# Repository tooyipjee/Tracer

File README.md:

# Tracer: A Wearable for Things 🚀

## High-Level Summary

Introducing "Tracer" - a dynamic, open-source project built on the ESP-32 platform. Tailored for enthusiasts and innovators, Tracer taps into the vast array of software libraries available for the ESP-32. It offers a unique window into the intricate processes and algorithms behind creating a personalized fitness tracker.

Available on 

---

## Detailed Description

### What is it?

Tracer is a versatile wearable designed for a myriad of applications. Whether you're a sports enthusiast wanting to analyze your tennis serve or a cyclist keen on understanding lean angles, Tracer provides invaluable insights. Key features include:

- **Real-time Object Tracking:** Utilize the LSM6DSL for precise motion capture.
- **Versatile Mounting:** High-quality velcro straps ensure adaptability, from monitoring lean angles on bicycles to analyzing tennis racquet poses.
- **Battery Management:** Efficient on-board Li-ion battery charging via the TP4065.
- **Extended Battery Life:** Up to 2.5 hours of continuous BLE streaming at 10Hz.
- **Proven Connectivity:** Boasts a 15m BLE range in open spaces, as tested on a tennis court.

---

## Use Cases

Tracer's design closely integrates with the Madgwick Filter, facilitating sensor fusion to estimate heading, roll, and pitch. This data can be transmitted to devices like smartphones or PCs for further analysis. Here are some applications:

## Use Cases

Tracer's design closely integrates with the Madgwick Filter, facilitating sensor fusion to estimate heading, roll, and pitch. This data can be transmitted to devices like smartphones or PCs for further analysis. Here are some applications:

- **Real-time 3D Visualization:** Stream data via UART to a script on [Processing](https://github.com/processing) for a 3D visual experience. Watch the demonstration [here](https://www.youtube.com/watch?v=f6d10yX7fZ4).

- **Stream to Phyphox:** Directly stream IMU plots over BLE to your phone. Export data as CSV for in-depth analysis, showcasing Tracer's capability to track accelerometer data and tennis ball strikes. Check out the live demo [here](https://www.youtube.com/watch?v=bZTHZ-QFxR4).

- **Gesture Recognition with Edge Impulse:** Highlighting Tracer's adaptability, the Edge Impulse platform can be employed to train a neural network. This network operates natively on the ESP32, tracking specific gestures or activities. See it in action [here](https://www.youtube.com/watch?v=aU7HlFeuip4).

---

## How to Run the Demo Script

1. **Setup:** Ensure you have the Arduino IDE installed on your computer.
2. **Connect:** Plug in your ESP32-C3 device to your computer via USB.
3. **Integrated JTAG:** Ensure the JTAG is setup. In Tools, "USB CDC On Boot" is Enabled and JTAG Adapter is USB JTAG Adapter.
5. **Load Script:** Open one of the demo script provided in the Arduino IDE.
6. **Select Board:** From the 'Tools' menu, select 'Board' and choose 'ESP32-C3'.
7. **Select Port:** Select the port for the Tracer device, if nothing pops up, unplug the device, hold the settings button and plug it back into the computer while still holding the button. It should appear now.
8. **Upload:** Click on the 'Upload' button to program the ESP32-C3.
9. **Monitor:** Open the Serial Monitor to view outputs and ensure the script runs successfully.

For any issues or further instructions, please refer to the documentation or raise an issue in the repo.

**Acknowledgments:** A special thank you to JLCPCB for their invaluable support in sponsoring this project. Their expertise has been instrumental, allowing for rapid prototyping without sacrificing quality.

---

## License

MIT License

Copyright (c) 2023 elektroThing

Permission is hereby granted, free of charge, to any person obtaining a copy
of this software and associated documentation files (the "Software"), to deal
in the Software without restriction, including without limitation the rights
to use, copy, modify, merge, publish, distribute, sublicense, and/or sell
copies of the Software, and to permit persons to whom the Software is
furnished to do so, subject to the following conditions:

The above copyright notice and this permission notice shall be included in all
copies or substantial portions of the Software.

THE SOFTWARE IS PROVIDED "AS IS", WITHOUT WARRANTY OF ANY KIND, EXPRESS OR
IMPLIED, INCLUDING BUT NOT LIMITED TO THE WARRANTIES OF MERCHANTABILITY,
FITNESS FOR A PARTICULAR PURPOSE AND NONINFRINGEMENT. IN NO EVENT SHALL THE
AUTHORS OR COPYRIGHT HOLDERS BE LIABLE FOR ANY CLAIM, DAMAGES OR OTHER
LIABILITY, WHETHER IN AN ACTION OF CONTRACT, TORT OR OTHERWISE, ARISING FROM,
OUT OF OR IN CONNECTION WITH THE SOFTWARE OR THE USE OR OTHER DEALINGS IN THE
SOFTWARE.

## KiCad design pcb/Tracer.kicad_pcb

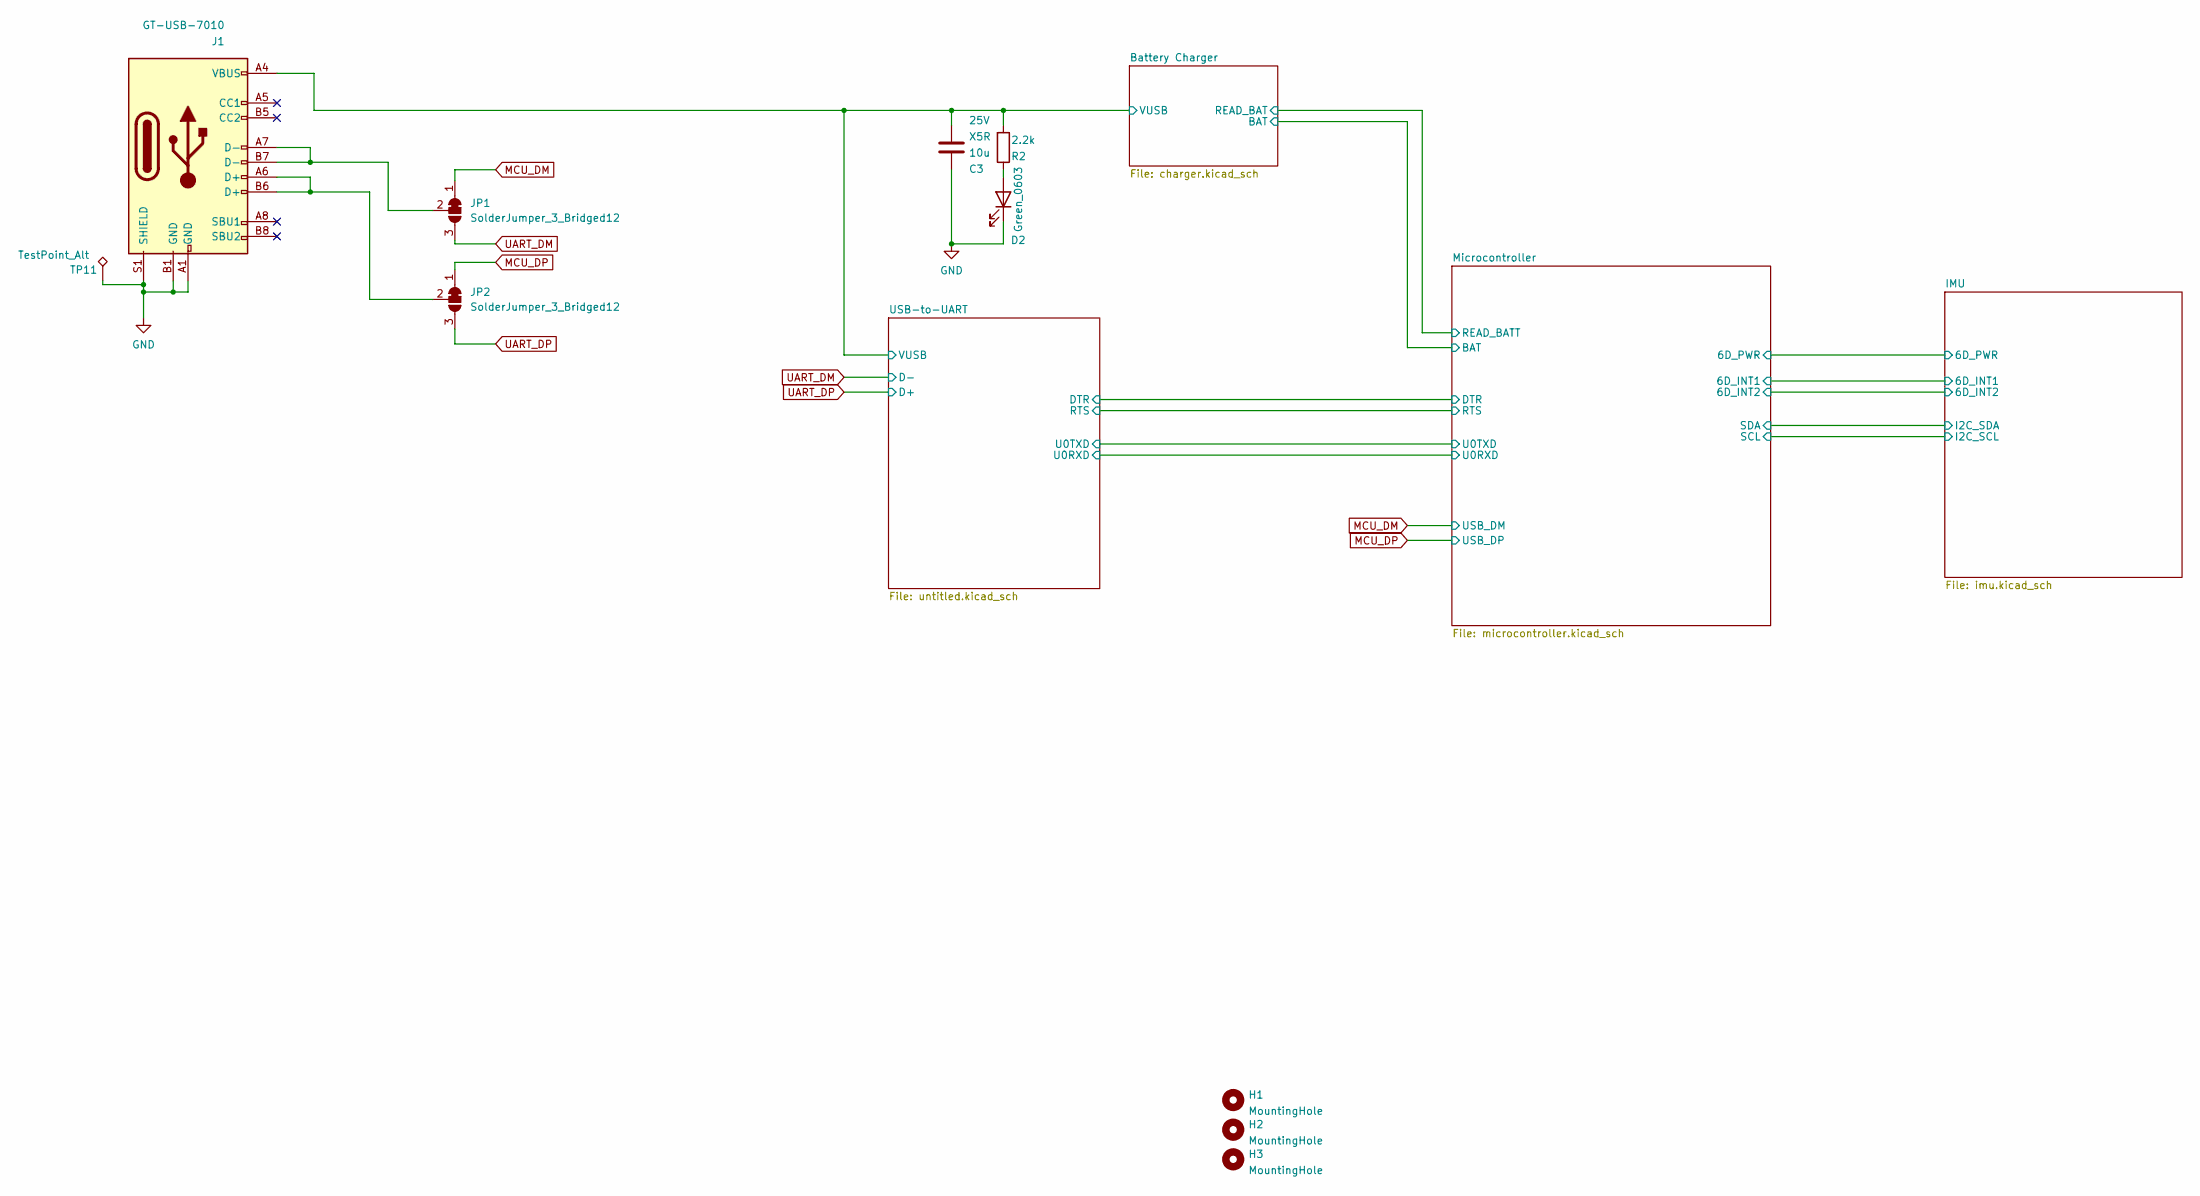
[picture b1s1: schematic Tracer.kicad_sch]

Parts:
C3: 10u; C_0805_2012Metric; Voltage 25V; LCSC C15850
D2: Green_0603; LED_0603_1608Metric; LCSC C72043
H1, H2, H3: MountingHole; MountingHole_2.2mm_M2_Small
J1: GT-USB-7010; GT-USB-7010A; LCSC C963370
JP1, JP2: SolderJumper_3_Bridged12; SolderJumper-3_P1.3mm_Bridged12_Pad1.0x1.5mm_NumberLabels
R2: 2.2k; R_0402_1005Metric; LCSC C25879
TP11: TestPoint_Alt; TestPoint_Pad_1.0x1.0mm

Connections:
/Battery Charger/VUSB: C3.2, J1.A4 (VBUS), J1.A9 (VBUS), J1.B4 (VBUS), J1.B9 (VBUS), R2.2; also elsewhere on the board
GND: C3.1, D2.1 (K), J1.A1 (GND), J1.B1 (GND), J1.S1 (SHIELD), TP11.1; also elsewhere on the board
MCU_DM: JP1.1 (A); also elsewhere on the board
MCU_DP: JP2.1 (A); also elsewhere on the board
unnamed: D2.2 (A), R2.1
unnamed: J1.A7 (D-), J1.B7 (D-), JP1.2 (C)
unnamed: J1.A6 (D+), J1.B6 (D+), JP2.2 (C)
UART_DM: JP1.3 (B); also elsewhere on the board
UART_DP: JP2.3 (B); also elsewhere on the board

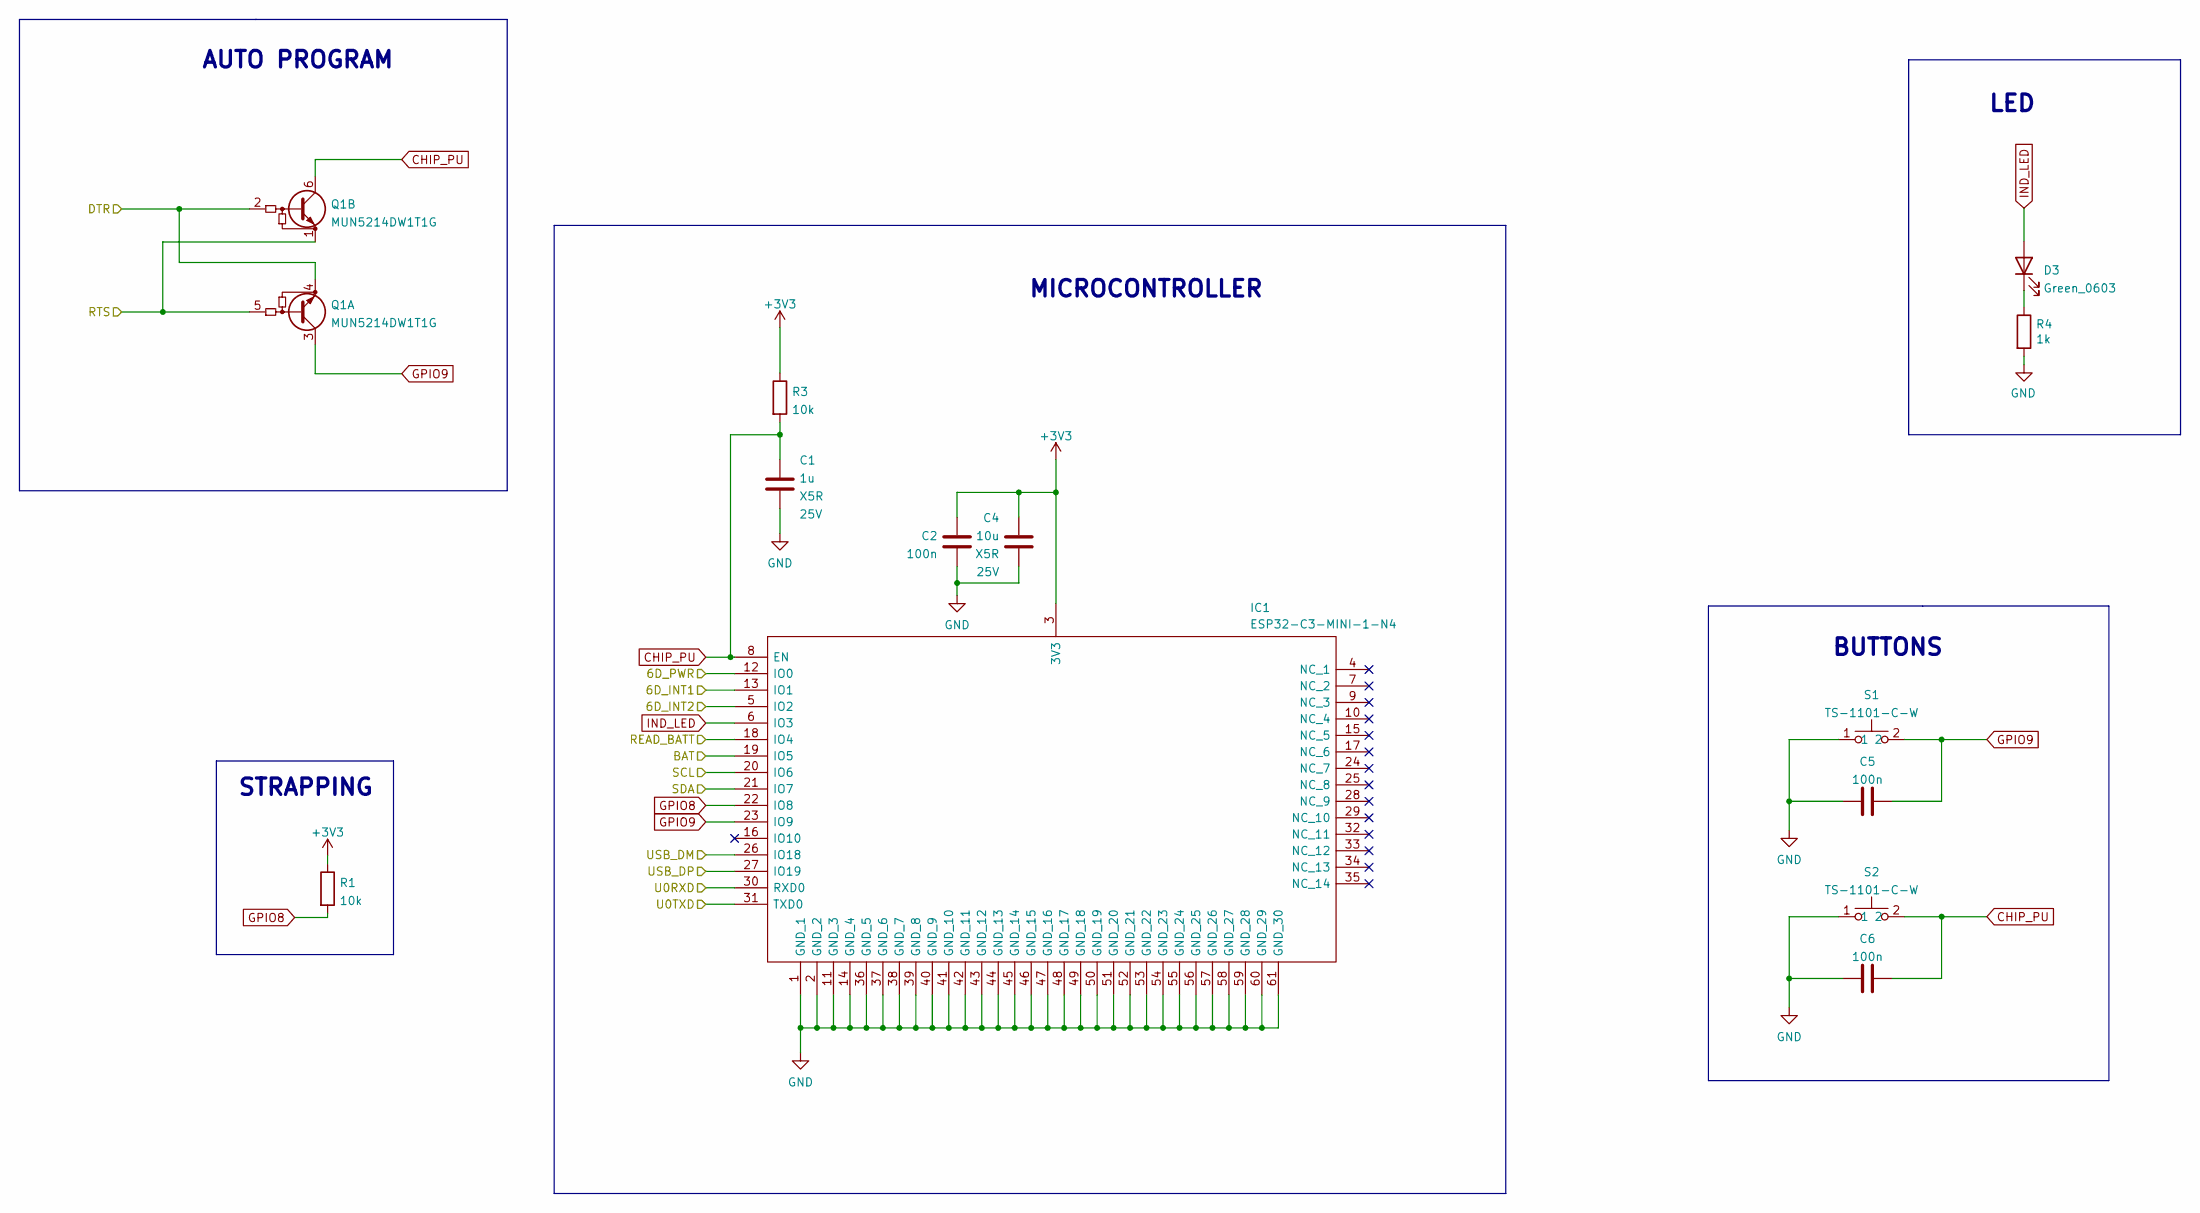
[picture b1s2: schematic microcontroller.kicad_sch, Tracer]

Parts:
C1: 1u; C_0402_1005Metric; Voltage 25V; LCSC C52923
C2, C5, C6: 100n; C_0402_1005Metric; LCSC C307331
C4: 10u; C_0805_2012Metric; Voltage 25V; LCSC C15850
D3: Green_0603; LED_0603_1608Metric; LCSC C72043
IC1: ESP32-C3-MINI-1-N4; ESP32C3MINI1N4; Manufacturer_Part_Number ESP32-C3-MINI-1-N4; Mouser Part Number 356-ESP32-C3-MINI1N4
Q1: MUN5214DW1T1G; SOT-363_SC-70-6; LCSC C94403
R1, R3: 10k; R_0402_1005Metric; LCSC C25744
R4: 1k; R_0402_1005Metric; LCSC C11702
S1, S2: TS-1101-C-W; TS1101CW; Manufacturer_Part_Number TS-1101-C-W; LCSC C318938

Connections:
+3V3: C2.1, C4.1, IC1.3 (3V3), R1.1, R3.1; also elsewhere on the board
/Battery Charger/BAT: IC1.19 (IO5); also elsewhere on the board
/Battery Charger/READ_BAT: IC1.18 (IO4); also elsewhere on the board
/IMU/6D_INT1: IC1.13 (IO1); also elsewhere on the board
/IMU/6D_INT2: IC1.5 (IO2); also elsewhere on the board
/IMU/6D_PWR: IC1.12 (IO0); also elsewhere on the board
/IMU/I2C_SCL: IC1.20 (IO6); also elsewhere on the board
/IMU/I2C_SDA: IC1.21 (IO7); also elsewhere on the board
/Microcontroller/DTR: Q1.2 (B2), Q1.4 (E1); also elsewhere on the board
/Microcontroller/RTS: Q1.1 (E2), Q1.5 (B1); also elsewhere on the board
/Microcontroller/U0RXD: IC1.30 (RXD0); also elsewhere on the board
/Microcontroller/U0TXD: IC1.31 (TXD0); also elsewhere on the board
CHIP_PU: C1.1, C6.2, IC1.8 (EN), Q1.6 (C2), R3.2, S2.2
GND: C1.2, C2.2, C4.2, C5.1, C6.1, IC1.1 (GND_1), IC1.2 (GND_2), IC1.11 (GND_3), IC1.14 (GND_4), IC1.36 (GND_5), IC1.37 (GND_6), IC1.38 (GND_7), IC1.39 (GND_8), IC1.40 (GND_9), IC1.41 (GND_10), IC1.42 (GND_11), IC1.43 (GND_12), IC1.44 (GND_13), IC1.45 (GND_14), IC1.46 (GND_15), IC1.47 (GND_16), IC1.48 (GND_17), IC1.49 (GND_18), IC1.50 (GND_19), IC1.51 (GND_20), IC1.52 (GND_21), IC1.53 (GND_22), IC1.54 (GND_23), IC1.55 (GND_24), IC1.56 (GND_25), IC1.57 (GND_26), IC1.58 (GND_27), IC1.59 (GND_28), IC1.60 (GND_29), IC1.61 (GND_30), R4.2, S1.1, S2.1; also elsewhere on the board
GPIO8: IC1.22 (IO8), R1.2
GPIO9: C5.2, IC1.23 (IO9), Q1.3 (C1), S1.2
IND_LED: D3.2 (A), IC1.6 (IO3)
MCU_DM: IC1.26 (IO18); also elsewhere on the board
MCU_DP: IC1.27 (IO19); also elsewhere on the board
unnamed: D3.1 (K), R4.1

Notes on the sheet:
MICROCONTROLLER
LED
AUTO PROGRAM
BUTTONS
STRAPPING

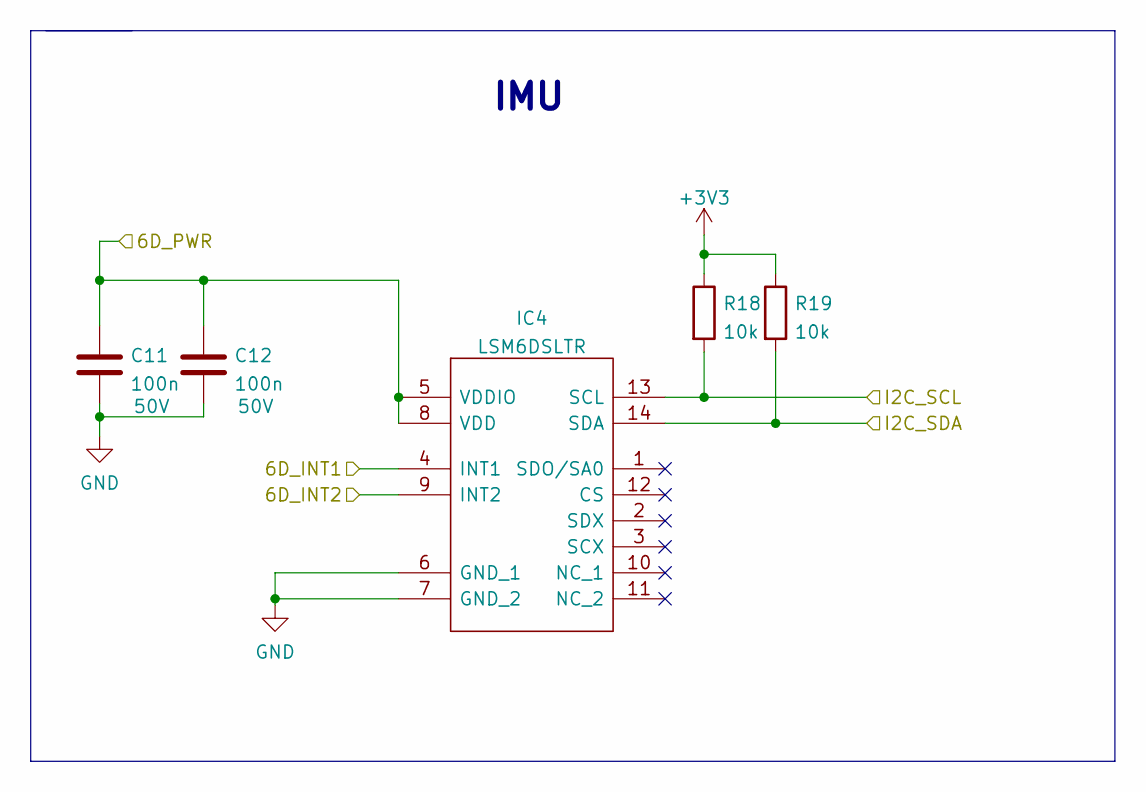
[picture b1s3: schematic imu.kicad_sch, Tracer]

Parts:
C11, C12: 100n; C_0402_1005Metric; Voltage 50V; LCSC C307331
IC4: LSM6DSLTR; Manufacturer_Part_Number LSM6DSLTR; Mouser Part Number 511-LSM6DSLTR
R18, R19: 10k; R_0402_1005Metric; LCSC C25744

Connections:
+3V3: R18.1, R19.1; also elsewhere on the board
/IMU/6D_INT1: IC4.4 (INT1); also elsewhere on the board
/IMU/6D_INT2: IC4.9 (INT2); also elsewhere on the board
/IMU/6D_PWR: C11.1, C12.1, IC4.5 (VDDIO), IC4.8 (VDD); also elsewhere on the board
/IMU/I2C_SCL: IC4.13 (SCL), R18.2; also elsewhere on the board
/IMU/I2C_SDA: IC4.14 (SDA), R19.2; also elsewhere on the board
GND: C11.2, C12.2, IC4.6 (GND_1), IC4.7 (GND_2); also elsewhere on the board

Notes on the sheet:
IMU

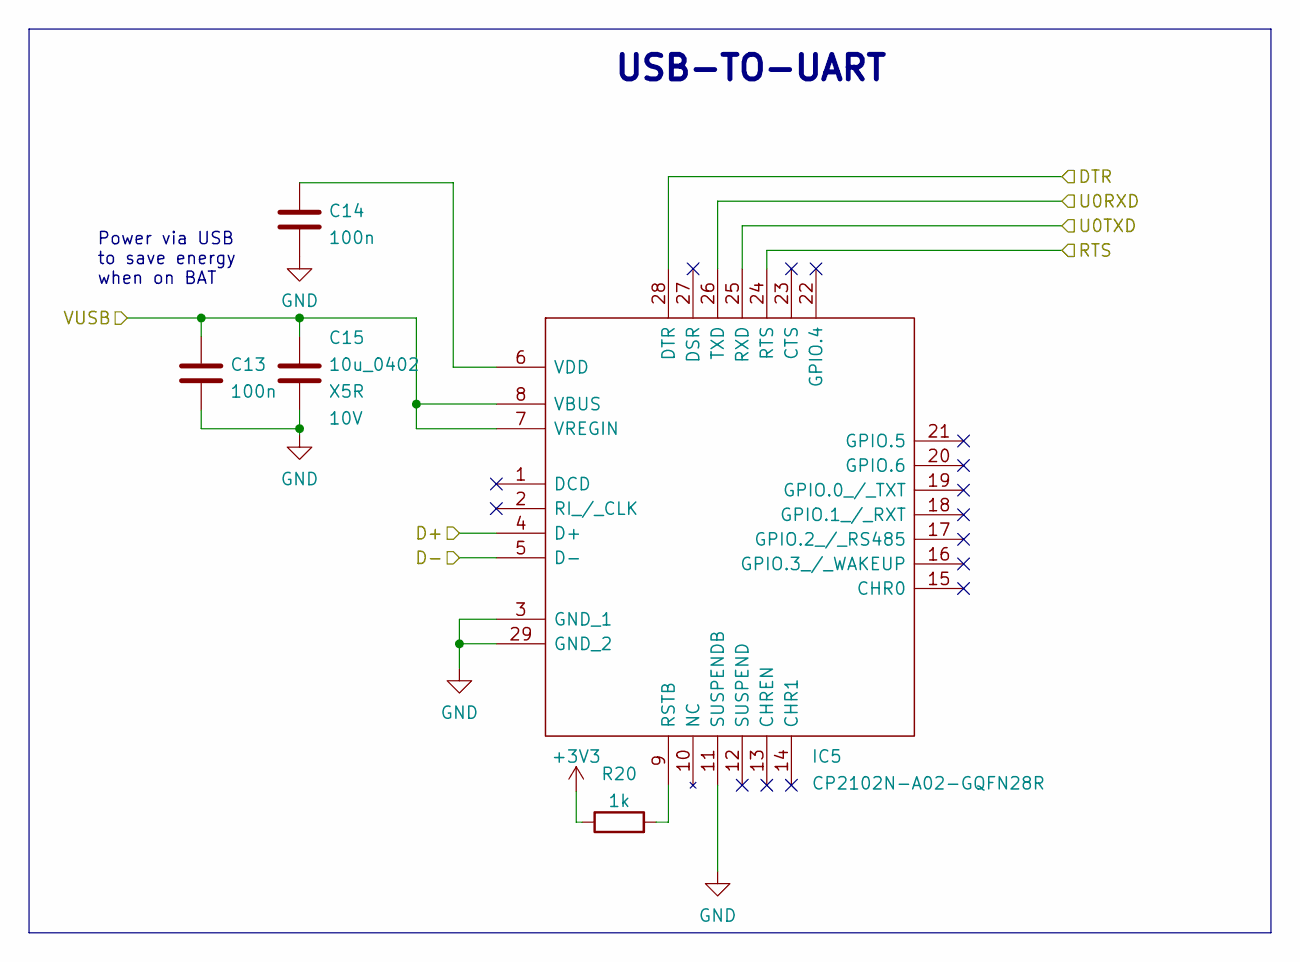
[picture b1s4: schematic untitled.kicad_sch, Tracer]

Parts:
C13, C14: 100n; C_0402_1005Metric; LCSC C307331
C15: 10u_0402; C_0402_1005Metric; Voltage 10V; LCSC C315248
IC5: CP2102N-A02-GQFN28R; QFN50P500X500X80-29N-D; Manufacturer_Part_Number CP2102N-A02-GQFN28R; Mouser Part Number 634-CP2102NA02QFN28R
R20: 1k; R_0402_1005Metric; LCSC C11702

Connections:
+3V3: R20.1; also elsewhere on the board
/Battery Charger/VUSB: C13.1, C15.1, IC5.7 (VREGIN), IC5.8 (VBUS); also elsewhere on the board
/Microcontroller/DTR: IC5.28 (DTR); also elsewhere on the board
/Microcontroller/RTS: IC5.24 (RTS); also elsewhere on the board
/Microcontroller/U0RXD: IC5.26 (TXD); also elsewhere on the board
/Microcontroller/U0TXD: IC5.25 (RXD); also elsewhere on the board
GND: C13.2, C14.2, C15.2, IC5.3 (GND_1), IC5.11 (SUSPENDB), IC5.29 (GND_2); also elsewhere on the board
unnamed: IC5.9 (RSTB), R20.2
unnamed: C14.1, IC5.6 (VDD)
UART_DM: IC5.5 (D-); also elsewhere on the board
UART_DP: IC5.4 (D+); also elsewhere on the board

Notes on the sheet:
USB-TO-UART
Power via USB to save energy when on BAT

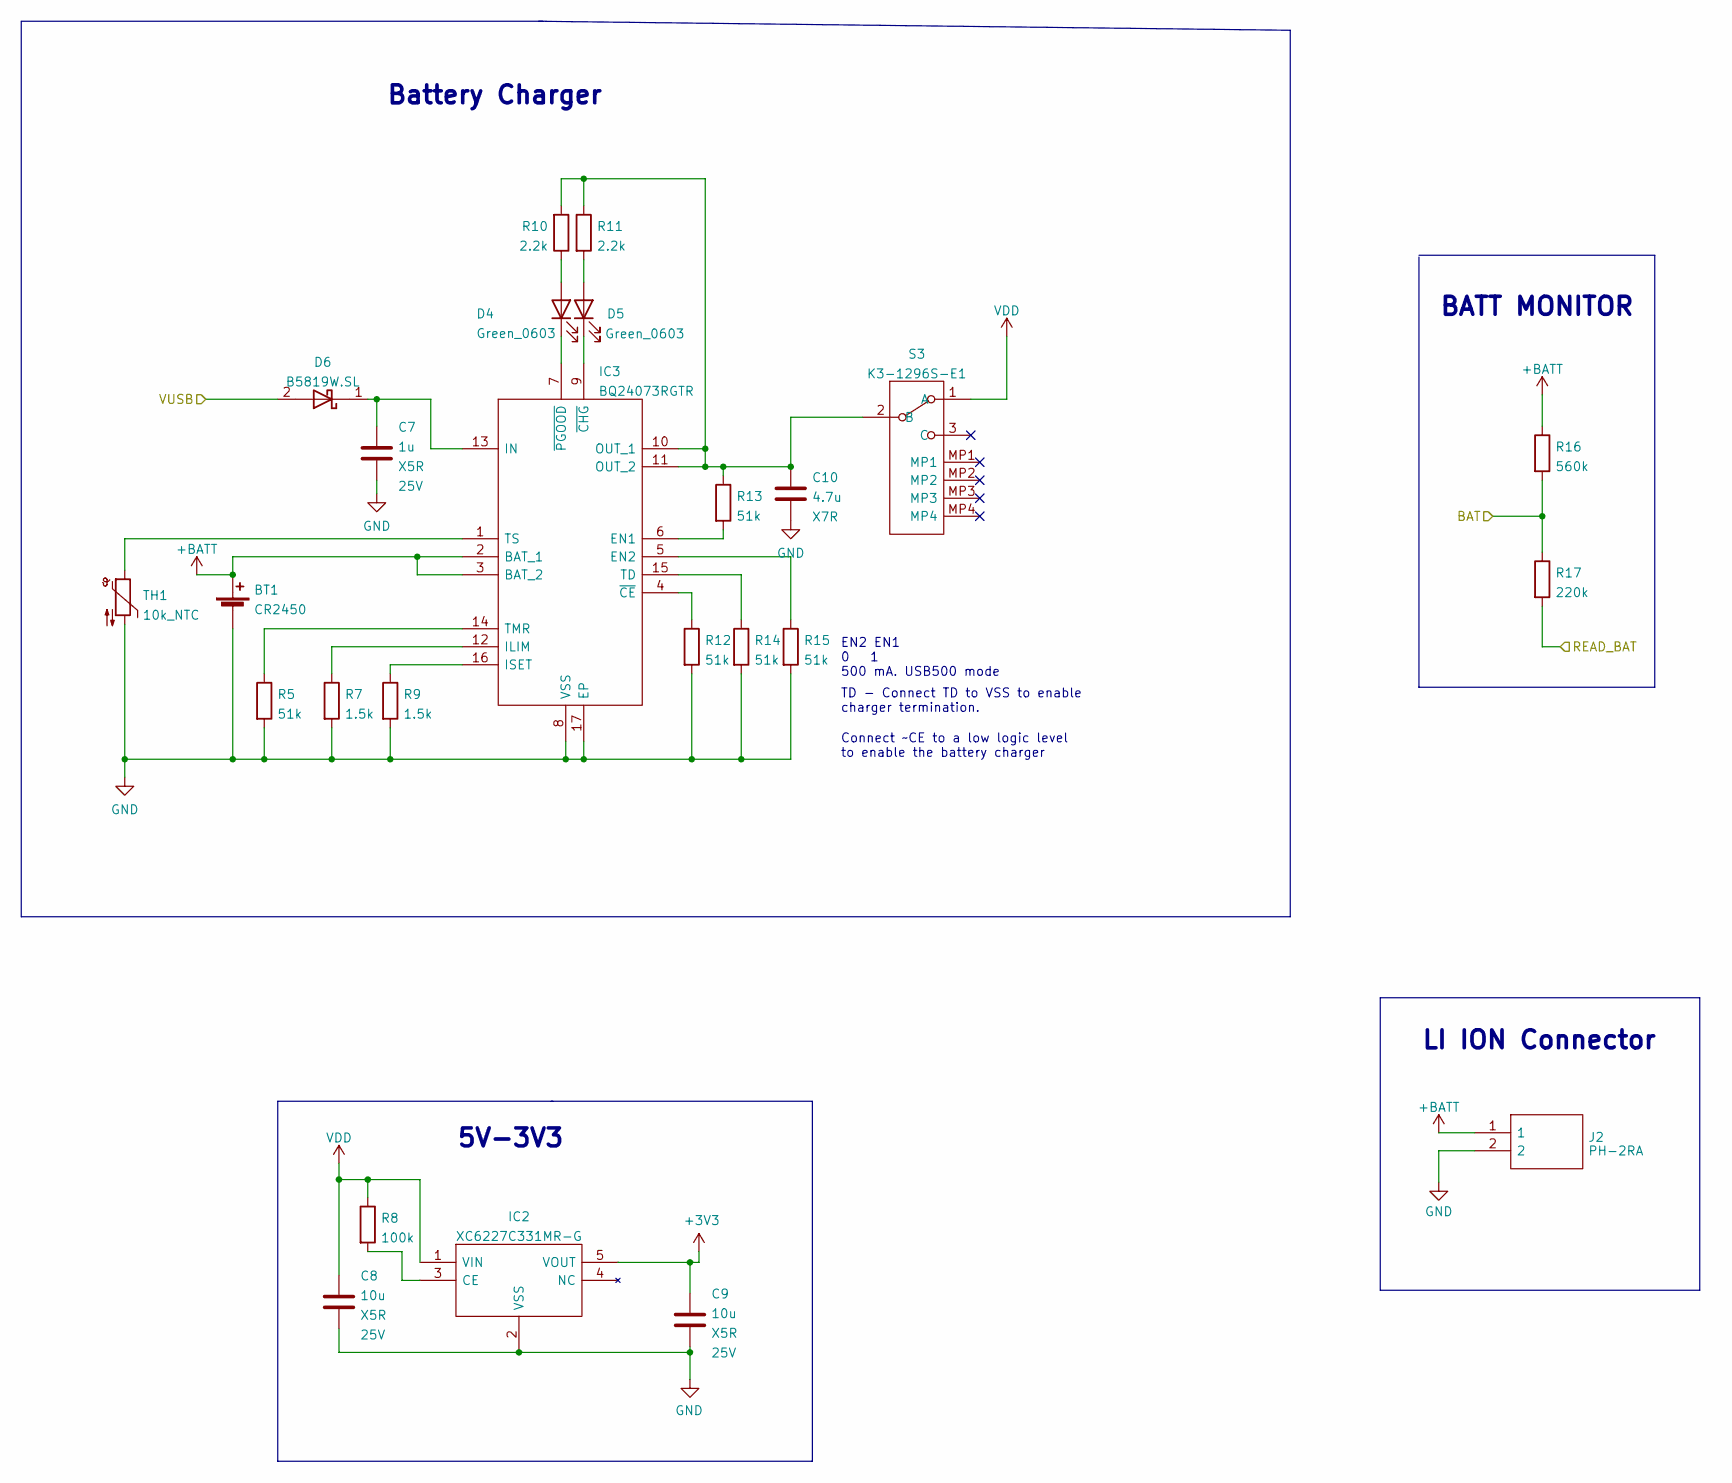
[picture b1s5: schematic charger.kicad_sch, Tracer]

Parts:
BT1: CR2450; BS-24-B4AK014; LCSC C964813
C7: 1u; C_0402_1005Metric; Voltage 25V; LCSC C52923
C8, C9: 10u; C_0805_2012Metric; Voltage 25V; LCSC C15850
C10: 4.7u; C_1206_3216Metric; Rating 50V; LCSC C29823
D4, D5: Green_0603; LED_0603_1608Metric; LCSC C72043
D6: B5819W.SL; B5819WSL; Manufacturer_Part_Number B5819W.SL; LCSC C8598
IC2: XC6227C331MR-G; SOT95P280X130-5N; Manufacturer_Part_Number XC6227C331MR-G; Mouser Part Number 865-XC6227C331MR-G
IC3: BQ24073RGTR; QFN50P300X300X100-17N-D; Manufacturer_Part_Number BQ24073RGTR; Mouser Part Number 595-BQ24073RGTR
J2: PH-2RA; SHDRRA2W50P0X200_1X2_600X760X510P; Manufacturer_Part_Number A2001WR-2P Thru-hole; Mouser Part Number 763-A2001WR2P
R5, R12, R13, R14, R15: 51k; R_0402_1005Metric; LCSC C25794
R7, R9: 1.5k; R_0402_1005Metric; LCSC C25867
R8: 100k; R_0402_1005Metric; LCSC C25741
R10, R11: 2.2k; R_0402_1005Metric; LCSC C25879
R16: 560k; R_0603_1608Metric; LCSC C23203
R17: 220k; R_0402_1005Metric; LCSC C25767
S3: K3-1296S-E1; K31296SE1; Manufacturer_Part_Number K3-1296S-E1; LCSC C128955
TH1: 10k_NTC; R_0402_1005Metric; MPN NCU15XH103F6SRC; LCSC C333993

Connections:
+3V3: C9.1, IC2.5 (VOUT); also elsewhere on the board
+BATT: BT1.1 (+), IC3.2 (BAT_1), IC3.3 (BAT_2), J2.1, R16.1
/Battery Charger/BAT: R16.2, R17.1; also elsewhere on the board
/Battery Charger/READ_BAT: R17.2; also elsewhere on the board
/Battery Charger/VUSB: D6.2; also elsewhere on the board
GND: BT1.2 (-), C7.2, C8.2, C9.2, C10.2, IC2.2 (VSS), IC3.8 (VSS), IC3.17 (EP), J2.2, R5.2, R7.2, R9.2, R12.2, R14.2, R15.2, TH1.2; also elsewhere on the board
unnamed: D4.2 (A), R10.1
unnamed: D4.1 (K), IC3.7 (~PGOOD)
unnamed: D5.2 (A), R11.2
unnamed: D5.1 (K), IC3.9 (~CHG)
unnamed: IC2.3 (CE), R8.2
unnamed: IC3.6 (EN1), R13.2
unnamed: IC3.5 (EN2), R15.1
unnamed: IC3.12 (ILIM), R7.1
unnamed: C7.1, D6.1, IC3.13 (IN)
unnamed: IC3.16 (ISET), R9.1
unnamed: C10.1, IC3.10 (OUT_1), IC3.11 (OUT_2), R10.2, R11.1, R13.1, S3.2 (B)
unnamed: IC3.15 (TD), R14.1
unnamed: IC3.14 (TMR), R5.1
unnamed: IC3.1 (TS), TH1.1
unnamed: IC3.4 (~CE), R12.1
VDD: C8.1, IC2.1 (VIN), R8.1, S3.1 (A)

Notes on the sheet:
TD - Connect TD to VSS to enable charger termination.
5V-3V3
EN2 EN1 0 1 500 mA. USB500 mode
LI ION Connector
Connect ~CE to a low logic level to enable the battery charger
BATT MONITOR
Battery Charger

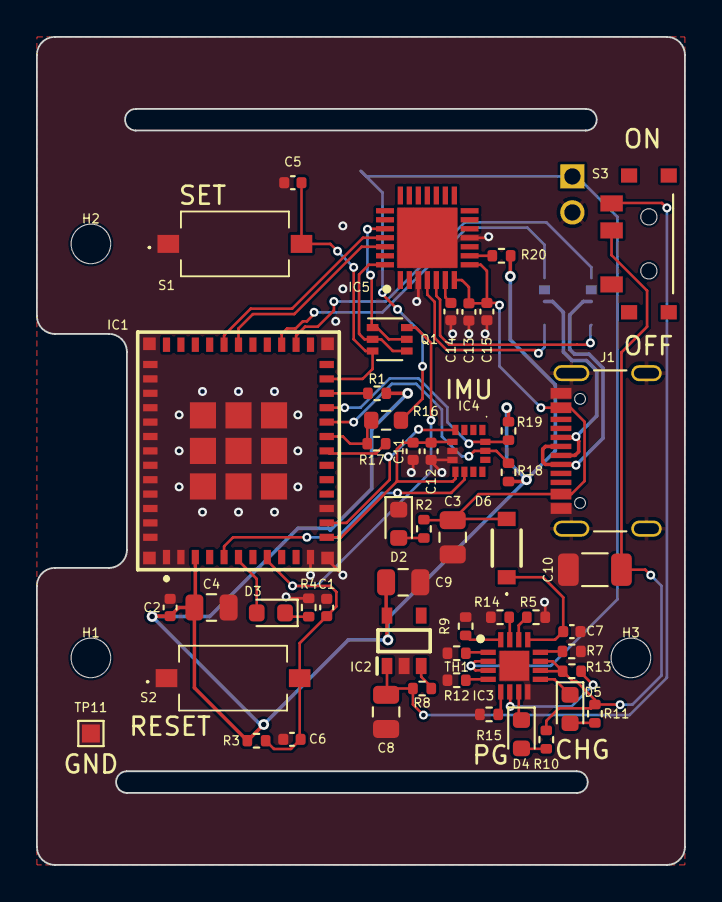
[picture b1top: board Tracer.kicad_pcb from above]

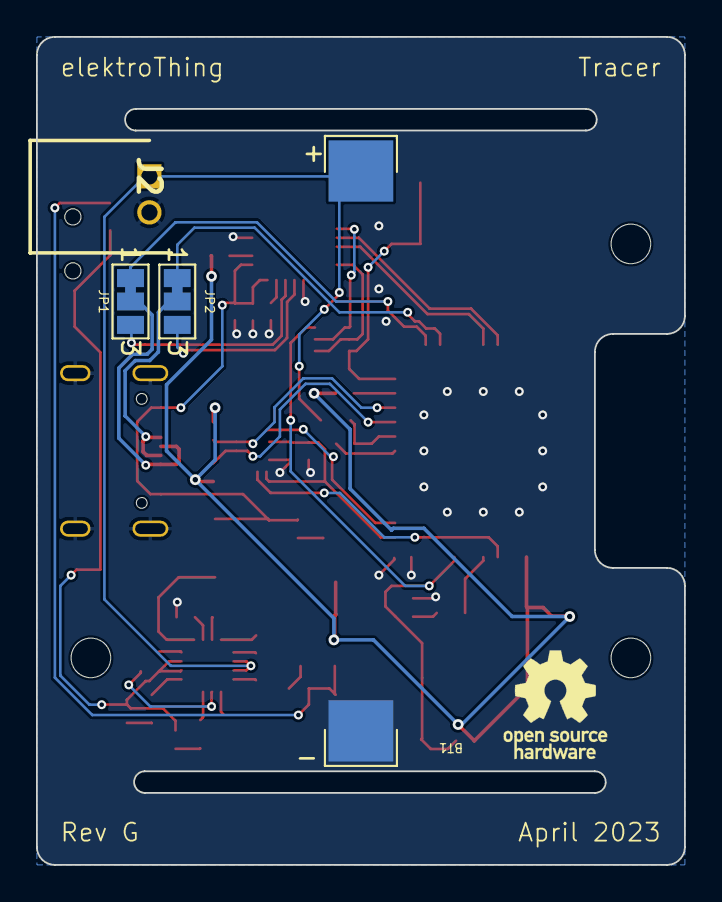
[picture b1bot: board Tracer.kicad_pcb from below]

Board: 4 copper layers, 36.0 x 46.0 mm, 58 parts (4 on the bottom side), 45 nets.

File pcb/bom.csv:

Designator,Footprint,Quantity,Value,LCSC Part #
BT1,BS-24-B4AK014,1,CR2450,C964813
"C1, C7",0402,2,1u,C52923
C10,1206,1,4.7u,C29823
"C11, C12, C13, C14, C2, C5, C6",0402,7,100n,C307331
C15,0402,1,10u_0402,C315248
"C3, C4, C8, C9",0805,4,10u,C15850
"D2, D3, D4, D5",0603,4,Green_0603,C72043
D6,B5819WSL,1,B5819W.SL,C8598
"H1, H2, H3",MountingHole_2.2mm_M2_Small,3,MountingHole,
IC1,ESP32C3MINI1N4,1,ESP32-C3-MINI-1-N4,C2838502
IC2,SOT95P280X130-5N,1,XC6227C331MR-G,C216640
IC3,QFN50P300X300X100-17N-D,1,BQ24073RGTR,C15220
IC4,LSM6DSLTR,1,LSM6DSLTR,C126672
IC5,QFN50P500X500X80-29N-D,1,CP2102N-A02-GQFN28R,C6568
J1,GT-USB-7010A,1,GT-USB-7010,C963370
J2,SHDRRA2W50P0X200_1X2_600X760X510P,1,PH-2RA,C225207
"JP1, JP2",SolderJumper-3_P1.3mm_Bridged12_Pad1.0x1.5mm_NumberLabels,2,SolderJumper_3_Bridged12,
Q1,SOT-363_SC-70-6,1,MUN5214DW1T1G,C94403
"R1, R18, R19, R3",0402,4,10k,C25744
"R10, R11, R2",0402,3,2.2k,C25879
"R12, R13, R14, R15, R5",0402,5,51k,C25794
R16,0603,1,560k,C23203
R17,0402,1,220k,C25767
"R20, R4",0402,2,1k,C11702
"R7, R9",0402,2,1.5k,C25867
R8,0402,1,100k,C25741
"S1, S2",TS1101CW,2,TS-1101-C-W,C318938
S3,K31296SE1,1,K3-1296S-E1,C128955
TH1,0402,1,10k_NTC,C333993
TP11,TestPoint_Pad_1.0x1.0mm,1,TestPoint_Alt,

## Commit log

2022-04-20 Added the setup section
2022-05-30 removed redundant software folder
2022-06-08 updated pinout
2022-06-08 updated with up to date images
2022-06-08 updated code and schematic
2022-06-09 updated src
2022-09-04 added BLE Serial
2023-08-13 Updated with latest rev
2023-08-13 Added image
2024-05-18 Migrating to public repo
